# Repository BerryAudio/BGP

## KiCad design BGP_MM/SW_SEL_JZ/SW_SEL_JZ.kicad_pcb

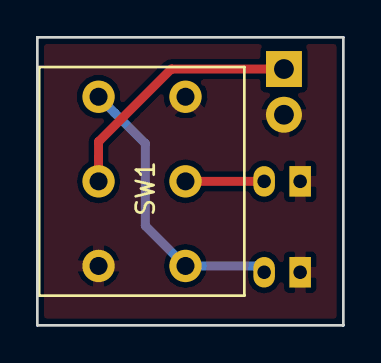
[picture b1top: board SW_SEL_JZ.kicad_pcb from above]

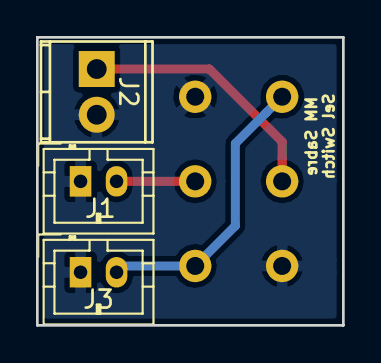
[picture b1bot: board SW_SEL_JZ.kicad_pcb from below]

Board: 2 copper layers, 17.0 x 16.0 mm, 4 parts (3 on the bottom side), 4 nets.

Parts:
J1, J3: Conn_01x02_Male; JST_PH_B2B-PH-K_02x2.00mm_Straight
J2: Screw_Terminal_01x02; TerminalBlock_Phoenix_MPT-2.54mm_2pol
SW1: Switch_SPDT_x2; NKK_DPDT

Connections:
/I_BR: J1.2, SW1.2
/I_NK: J2.1, SW1.5
/SIG_O: J3.2, SW1.3, SW1.4
Earth: J1.1, J2.2, J3.1, SW1.1, SW1.6

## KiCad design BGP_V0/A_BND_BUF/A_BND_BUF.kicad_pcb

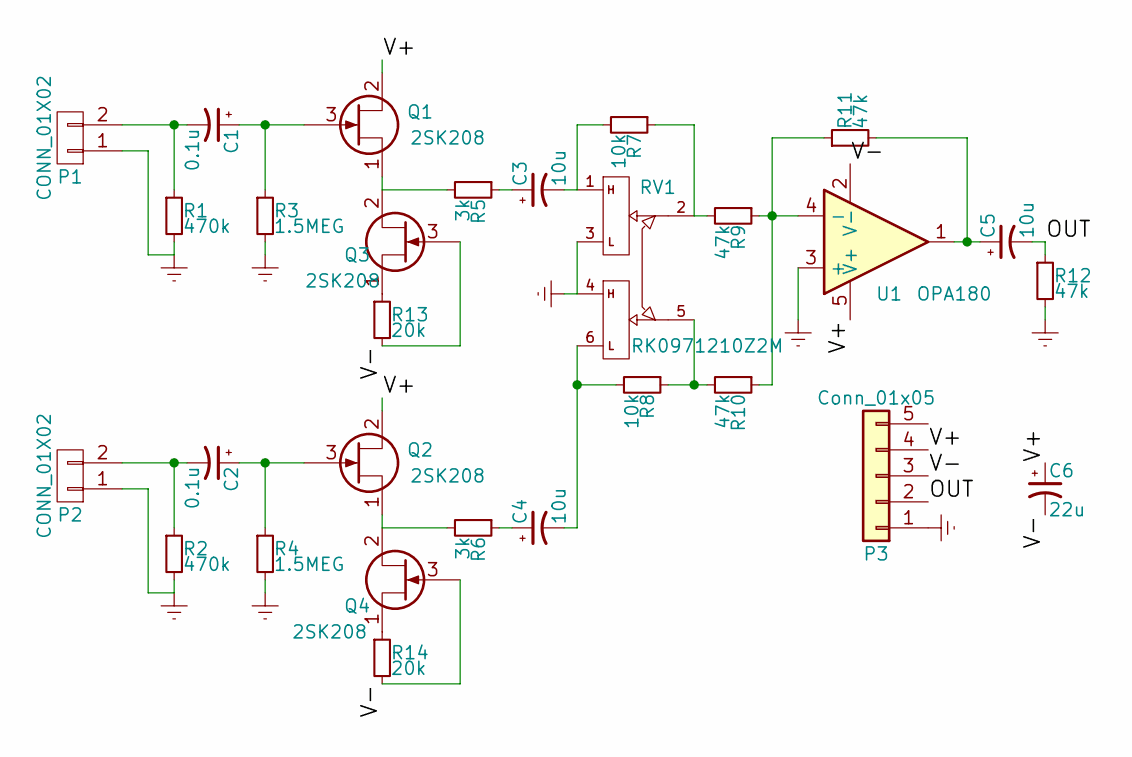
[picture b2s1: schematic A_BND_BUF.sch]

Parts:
C1, C2: 0.1u; TantalC_SizeR_EIA-2012
C3, C4, C5: 10u; TantalC_SizeS_EIA-3216
C6: 22u; C_0805_HandSoldering
P1, P2: CONN_01X02; TerminalBlock_Pheonix_MPT-2.54mm_2pol
P3: Conn_01x05; Molex_MicroLatch-53253-0570_05x2.00mm_Straight
Q1, Q2, Q3, Q4: 2SK208; SC-59_Handsoldering
R1, R2: 470k; R_0603_HandSoldering
R3, R4: 1.5MEG; R_0603_HandSoldering
R5, R6: 3k; R_0603_HandSoldering
R7, R8: 10k; R_0603_HandSoldering
R9, R10, R11, R12: 47k; R_0603_HandSoldering
R13, R14: 20k; R_0603_HandSoldering
RV1: RK0971210Z2M; Potentiometer_Alps_RK097_Double_Vertical
U1: OPA180; SOT-23-5_HandSoldering

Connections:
/OUT: C5.2, P3.2, R12.1
/V+: C6.1, P3.4, Q1.2 (D), Q2.2 (D), U1.5 (V+)
/V-: C6.2, P3.3, Q3.3 (G), Q4.3 (G), R13.2, R14.2, U1.2 (V-)
Earth: P1.1, P2.1, P3.1, R1.2, R2.2, R3.2, R4.2, R12.2, RV1.3, RV1.4, U1.3 (+)
unnamed: C1.1, Q1.3 (G), R3.1
unnamed: C1.2, P1.2, R1.1
unnamed: C2.1, Q2.3 (G), R4.1
unnamed: C2.2, P2.2, R2.1
unnamed: C3.1, R5.1
unnamed: C3.2, R7.2, RV1.1
unnamed: C4.1, R6.1
unnamed: C4.2, R8.2, RV1.6
unnamed: C5.1, R11.2, U1.1
unnamed: Q1.1 (S), Q3.2 (D), R5.2
unnamed: Q2.1 (S), Q4.2 (D), R6.2
unnamed: Q3.1 (S), R13.1
unnamed: Q4.1 (S), R14.1
unnamed: R7.1, R9.2, RV1.2
unnamed: R9.1, R10.1, R11.1, U1.4 (-)
unnamed: R8.1, R10.2, RV1.5

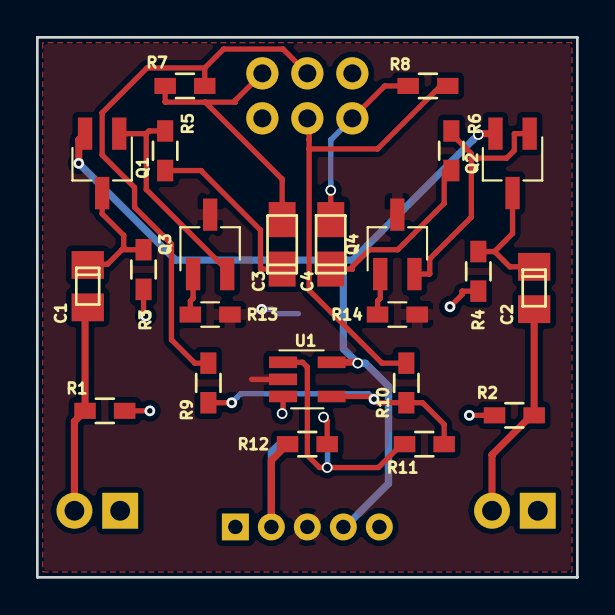
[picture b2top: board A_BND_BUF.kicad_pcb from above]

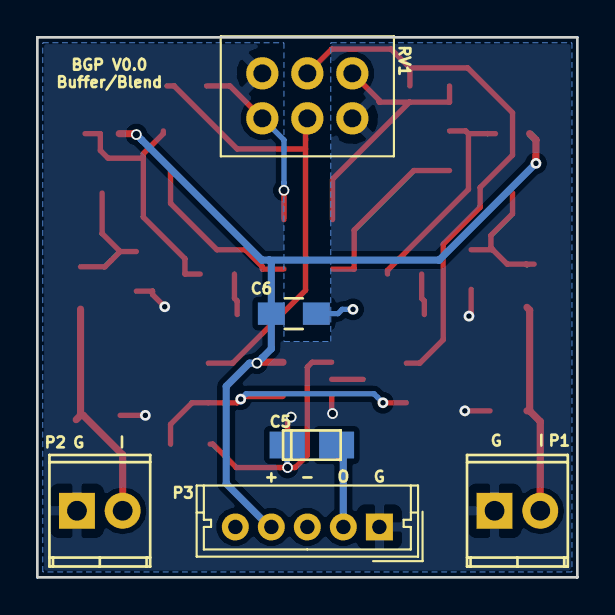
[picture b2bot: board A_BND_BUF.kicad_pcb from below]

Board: 2 copper layers, 30.0 x 30.0 mm, 29 parts (6 on the bottom side), 20 nets.

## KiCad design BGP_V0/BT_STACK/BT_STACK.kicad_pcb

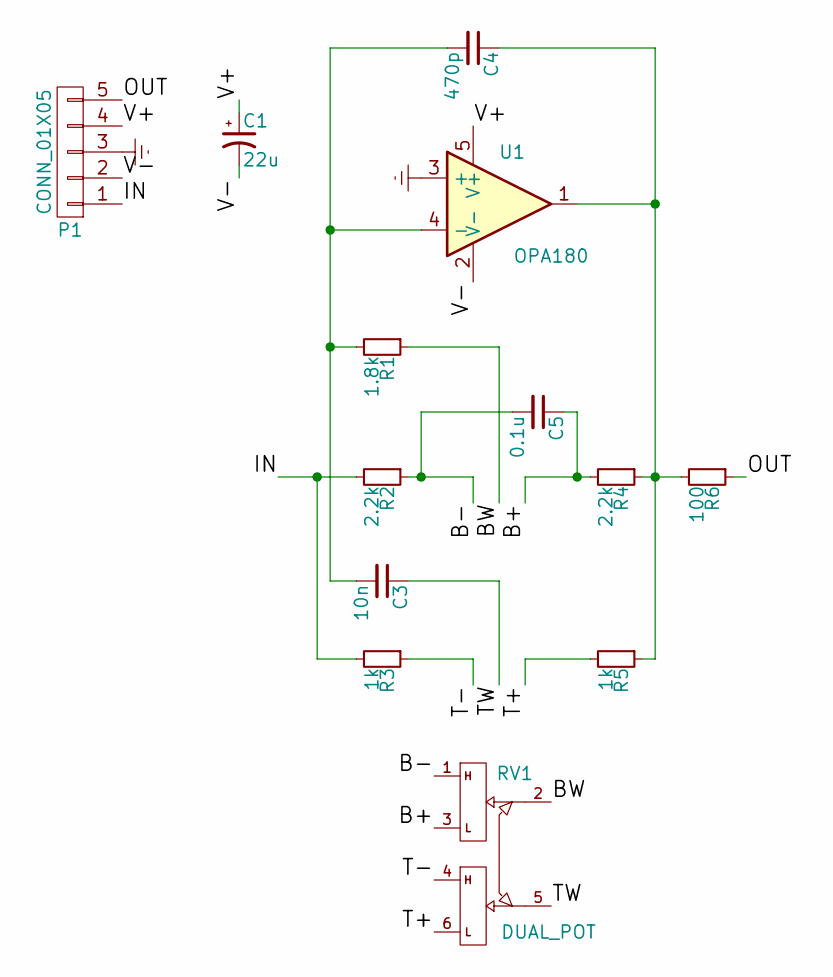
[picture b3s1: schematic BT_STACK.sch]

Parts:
C1: 22u; C_0805_HandSoldering
C3: 10n; C_0805_HandSoldering
C4: 470p; C_0805_HandSoldering
C5: 0.1u; C_0805_HandSoldering
P1: CONN_01X05; Molex_MicroLatch-53253-0570_05x2.00mm_Straight
R1: 1.8k; R_0603_HandSoldering
R2, R4: 2.2k; R_0603_HandSoldering
R3, R5: 1k; R_0603_HandSoldering
R6: 100; R_0603_HandSoldering
RV1: DUAL_POT; Potentiometer_Alps_RK097_Double_Vertical_Dual_Shaft
U1: OPA180; SOT-23-5_HandSoldering

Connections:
/B+: C5.1, R4.2, RV1.3
/B-: C5.2, R2.1, RV1.1
/BW: R1.1, RV1.2
/IN: P1.1, R2.2, R3.2
/OUT: P1.5, R6.1
/T+: R5.2, RV1.6
/T-: R3.1, RV1.4
/TW: C3.1, RV1.5
/V+: C1.1, P1.4, U1.5 (V+)
/V-: C1.2, P1.2, U1.2 (V-)
Earth: P1.3, U1.3 (+)
unnamed: C3.2, C4.2, R1.2, U1.4 (-)
unnamed: C4.1, R4.1, R5.1, R6.2, U1.1

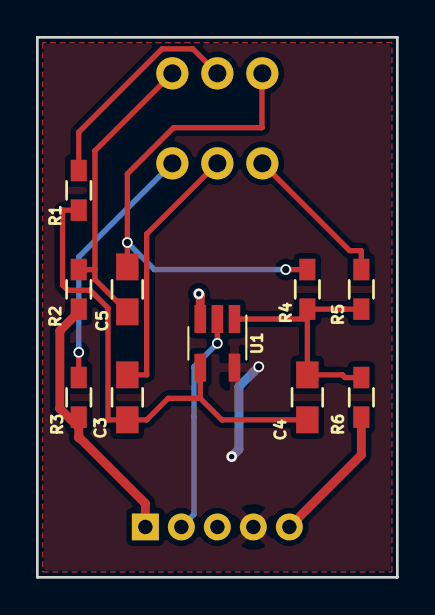
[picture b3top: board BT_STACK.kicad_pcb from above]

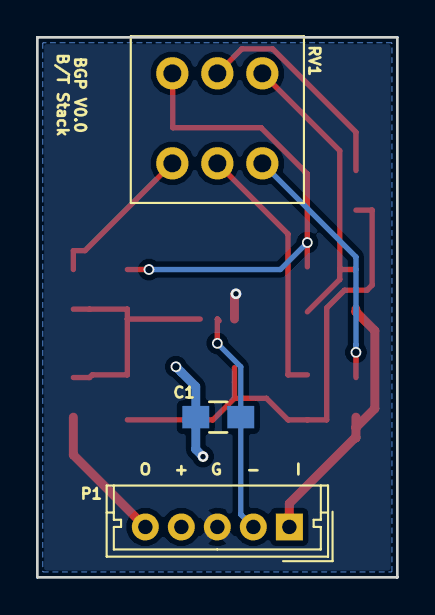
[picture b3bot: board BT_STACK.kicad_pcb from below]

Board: 2 copper layers, 20.0 x 30.0 mm, 13 parts (3 on the bottom side), 13 nets.

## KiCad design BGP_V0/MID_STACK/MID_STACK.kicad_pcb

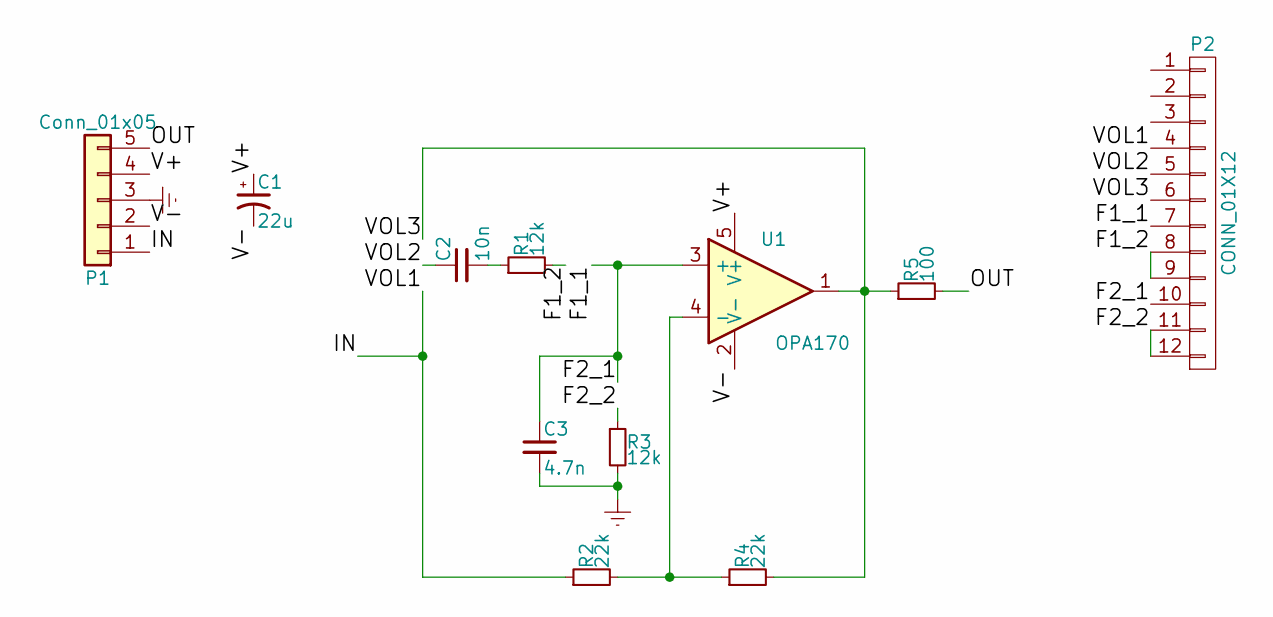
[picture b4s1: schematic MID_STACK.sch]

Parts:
C1: 22u; C_1206_HandSoldering
C2: 10n; C_0805_HandSoldering
C3: 4.7n; C_0805_HandSoldering
P1: Conn_01x05; Molex_MicroLatch-53253-0570_05x2.00mm_Straight
P2: CONN_01X12; Potentiometer_Alps_RK097_Quad_Vertical_Dual_Shaft
R1, R3: 12k; R_0603_HandSoldering
R2, R4: 22k; R_0603_HandSoldering
R5: 100; R_0603_HandSoldering
U1: OPA170; SOT-23-5_HandSoldering

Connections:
/F1_1: C3.1, P2.7, P2.10, U1.3 (+)
/F1_2: P2.8, P2.9, R1.2
/F2_2: P2.11, P2.12, R3.1
/IN: P1.1, P2.4, R2.1
/OUT: P1.5, R5.2
/V+: C1.1, P1.4, U1.5 (V+)
/V-: C1.2, P1.2, U1.2 (V-)
/VOL2: C2.1, P2.5
/VOL3: P2.6, R4.2, R5.1, U1.1
Earth: C3.2, P1.3, R3.2
unnamed: C2.2, R1.1
unnamed: R2.2, R4.1, U1.4 (-)

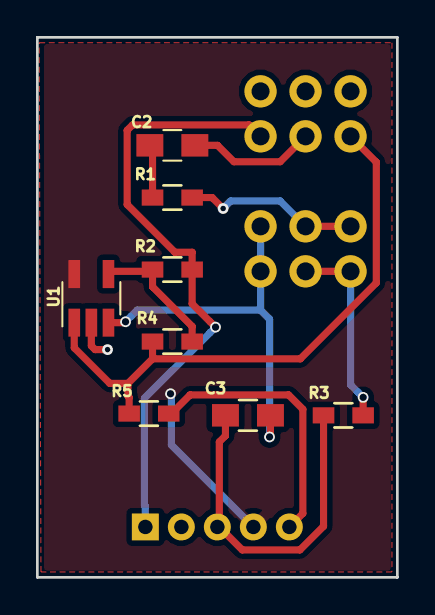
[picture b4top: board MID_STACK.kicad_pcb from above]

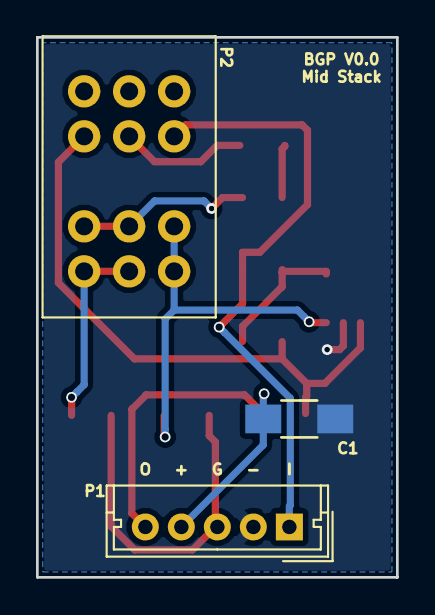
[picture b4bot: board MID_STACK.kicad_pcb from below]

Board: 2 copper layers, 20.0 x 30.0 mm, 11 parts (3 on the bottom side), 12 nets.

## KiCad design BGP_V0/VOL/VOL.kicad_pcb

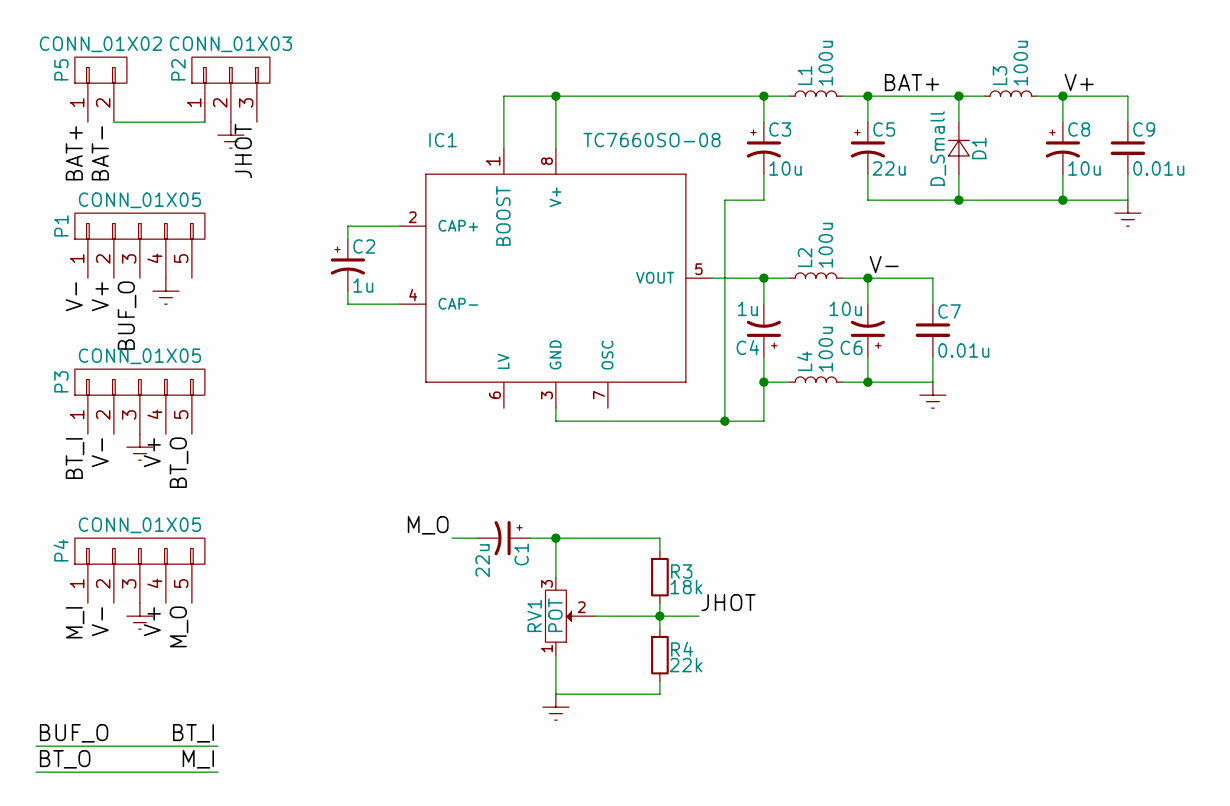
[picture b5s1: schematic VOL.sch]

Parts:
C1: 22u; TantalC_SizeR_EIA-2012
C2, C4: 1u; C_0805_HandSoldering
C3, C6, C8: 10u; C_0805_HandSoldering
C5: 22u; C_0805_HandSoldering
C7, C9: 0.01u; C_0603_HandSoldering
D1: D_Small; SOD-123
IC1: TC7660SO-08; SOIC-8_3.9x4.9mm_Pitch1.27mm
L1, L2, L3, L4: 100u; C_0805_HandSoldering
P1, P3, P4: CONN_01X05; Molex_MicroLatch-53253-0570_05x2.00mm_Straight
P2: CONN_01X03; TerminalBlock_Pheonix_MPT-2.54mm_3pol
P5: CONN_01X02; TerminalBlock_Pheonix_MPT-2.54mm_2pol
R3: 18k; R_0603_HandSoldering
R4: 22k; R_0603_HandSoldering
RV1: POT; Potentiometer_Alps_RK097_Single_Vertical

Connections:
/BAT+: C5.1, D1.1 (K), L1.2, L3.1, P5.1
/BAT-: P2.1, P5.2
/BT_I: P1.3, P3.1
/BT_O: P3.5, P4.1
/JHOT: P2.3, R3.2, R4.1, RV1.2
/M_O: C1.2, P4.5
/V+: C8.1, C9.1, L3.2, P1.2, P3.4, P4.4
/V-: C6.2, C7.1, L2.2, P1.1, P3.2, P4.2
Earth: C5.2, C6.1, C7.2, C8.2, C9.2, D1.2 (A), L4.2, P1.4, P2.2, P3.3, P4.3, R4.2, RV1.1
unnamed: C1.1, R3.1, RV1.3
unnamed: C2.1, IC1.2 (CAP+)
unnamed: C2.2, IC1.4 (CAP-)
unnamed: C3.1, IC1.1 (BOOST), IC1.8 (V+), L1.1
unnamed: C3.2, C4.1, IC1.3 (GND), L4.1
unnamed: C4.2, IC1.5 (VOUT), L2.1

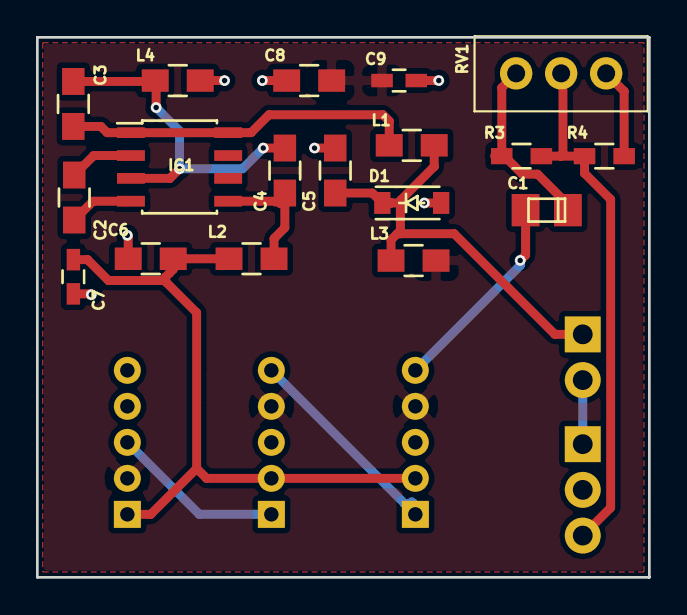
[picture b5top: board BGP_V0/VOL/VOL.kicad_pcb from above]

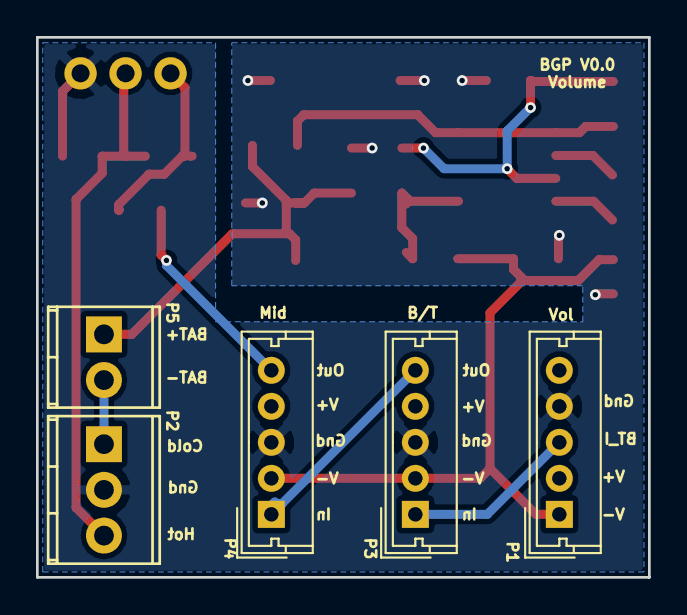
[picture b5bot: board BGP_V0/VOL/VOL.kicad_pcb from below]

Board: 2 copper layers, 34.0 x 30.0 mm, 23 parts (5 on the bottom side), 15 nets.

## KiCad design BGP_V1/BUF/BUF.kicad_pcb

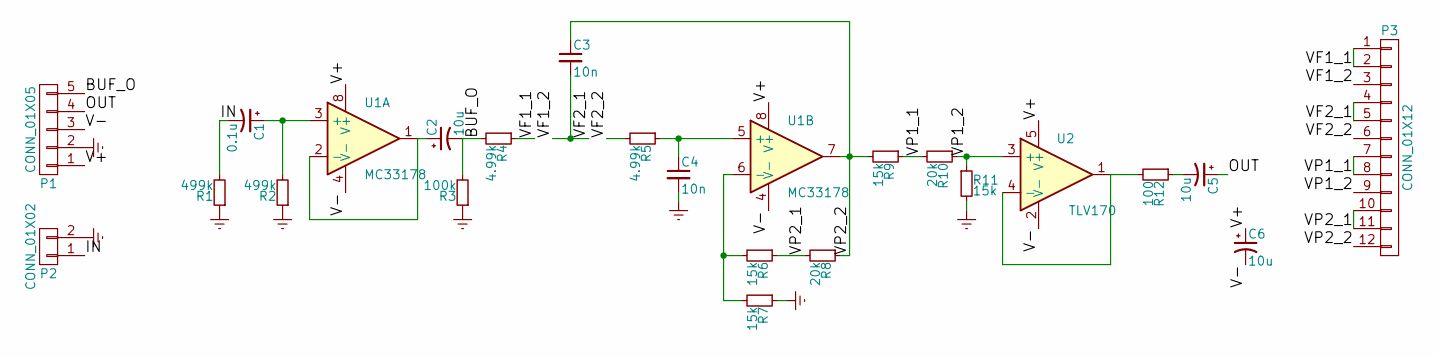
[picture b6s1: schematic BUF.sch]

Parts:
C1: 0.1u; C_0805_HandSoldering
C2, C5: 10u; TantalC_SizeS_EIA-3216
C3, C4: 10n; C_0805_HandSoldering
C6: 10u; C_0805_HandSoldering
P1: CONN_01X05; Molex_MicroLatch-53253-0570_05x2.00mm_Straight
P2: CONN_01X02; TerminalBlock_Pheonix_MPT-2.54mm_2pol
P3: CONN_01X12; Potentiometer_Alps_RK097_Quad_Vertical_Dual_Shaft
R1, R2: 499k; R_0603_HandSoldering
R3: 100k; R_0603_HandSoldering
R4, R5: 4.99k; R_0603_HandSoldering
R6, R7, R9, R11: 15k; R_0603_HandSoldering
R8, R10: 20k; R_0603_HandSoldering
R12: 100; R_0603_HandSoldering
U1: MC33178; SOIC-8_3.9x4.9mm_Pitch1.27mm
U2: TLV170; SOT-23-5_HandSoldering

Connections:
/BUF_O: C2.2, P1.5, R3.2, R4.2
/IN: C1.2, P2.1, R1.2
/OUT: C5.1, P1.4
/V+: C6.1, P1.1, U1.8 (V+), U2.5 (V+)
/V-: C6.2, P1.3, U1.4 (V-), U2.2 (V-)
/VF1_1: P3.1, P3.2, R4.1
/VF1_2: C3.2, P3.3, P3.4, P3.5
/VF2_2: P3.6, R5.2
/VP1_1: P3.7, P3.8, R9.1, R10.2
/VP1_2: P3.9, R10.1, R11.1, U2.3 (+)
/VP2_1: P3.10, P3.11, R6.1, R8.2
/VP2_2: C3.1, P3.12, R8.1, R9.2, U1.7
Earth: C4.2, P1.2, P2.2, R1.1, R2.1, R3.1, R7.1, R11.2
unnamed: C1.1, R2.2, U1.3 (+)
unnamed: C2.1, U1.1, U1.2 (-)
unnamed: C4.1, R5.1, U1.5 (+)
unnamed: C5.2, R12.1
unnamed: R6.2, R7.2, U1.6 (-)
unnamed: R12.2, U2.1, U2.4 (-)

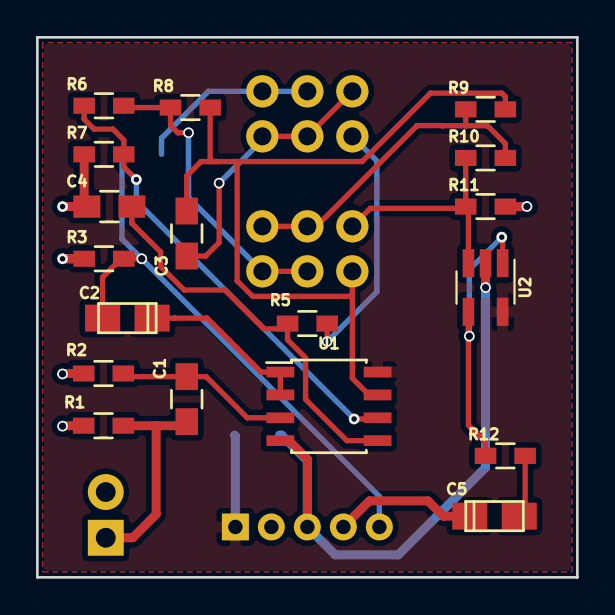
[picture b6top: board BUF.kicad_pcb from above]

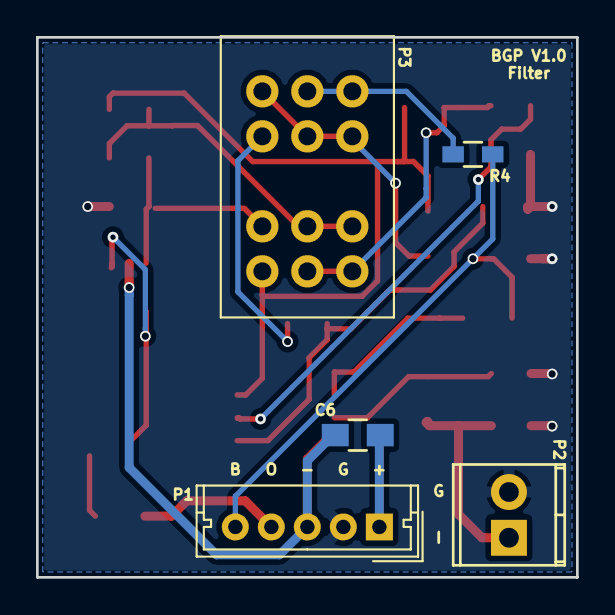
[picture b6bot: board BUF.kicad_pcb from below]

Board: 2 copper layers, 30.0 x 30.0 mm, 23 parts (5 on the bottom side), 19 nets.

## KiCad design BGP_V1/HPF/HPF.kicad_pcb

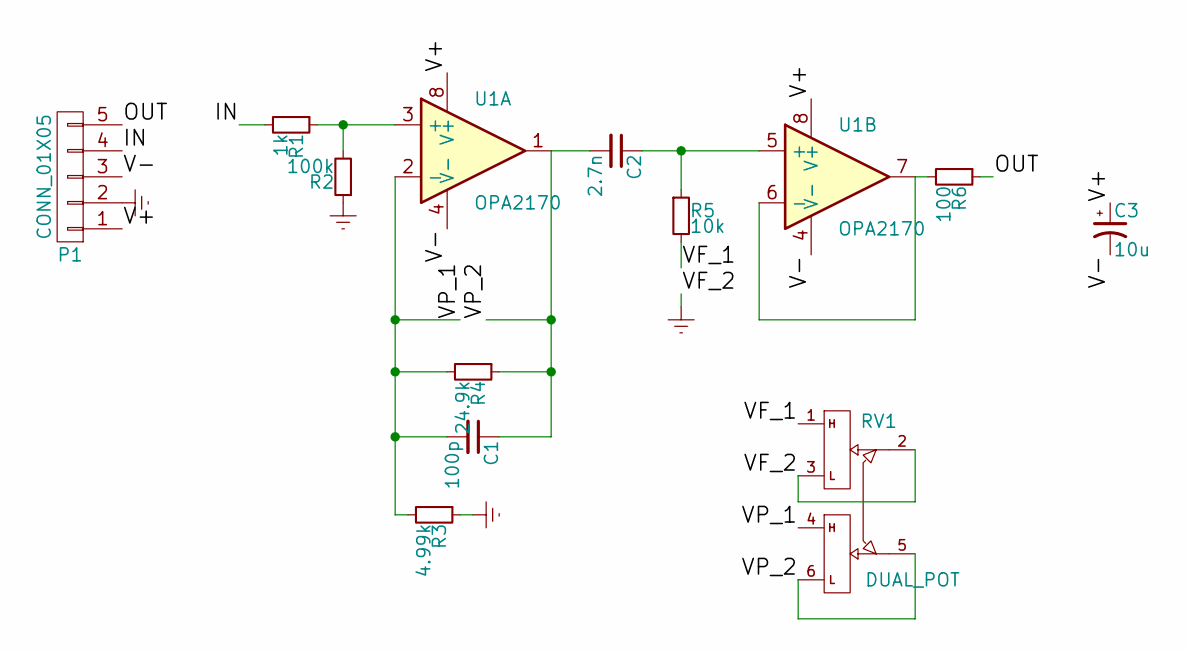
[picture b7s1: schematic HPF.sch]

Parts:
C1: 100p; C_0805_HandSoldering
C2: 2.7n; C_0805_HandSoldering
C3: 10u; C_0805_HandSoldering
P1: CONN_01X05; Molex_MicroLatch-53253-0570_05x2.00mm_Straight
R1: 1k; R_0603_HandSoldering
R2: 100k; R_0603_HandSoldering
R3: 4.99k; R_0603_HandSoldering
R4: 24.9k; R_0603_HandSoldering
R5: 10k; R_0603_HandSoldering
R6: 100; R_0603_HandSoldering
RV1: DUAL_POT; Potentiometer_Alpha_Double_Vertical_Dual_Shaft
U1: OPA2170; SOIC-8_3.9x4.9mm_Pitch1.27mm

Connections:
/IN: P1.4, R1.2
/OUT: P1.5, R6.1
/V+: C3.1, P1.1, U1.8 (V+)
/V-: C3.2, P1.3, U1.4 (V-)
/VF_1: R5.2, RV1.1
/VP_1: C1.2, R3.2, R4.2, RV1.4, U1.2 (-)
/VP_2: C1.1, C2.2, R4.1, RV1.5, RV1.6, U1.1
Earth: P1.2, R2.1, R3.1, RV1.2, RV1.3
unnamed: C2.1, R5.1, U1.5 (+)
unnamed: R1.1, R2.2, U1.3 (+)
unnamed: R6.2, U1.6 (-), U1.7

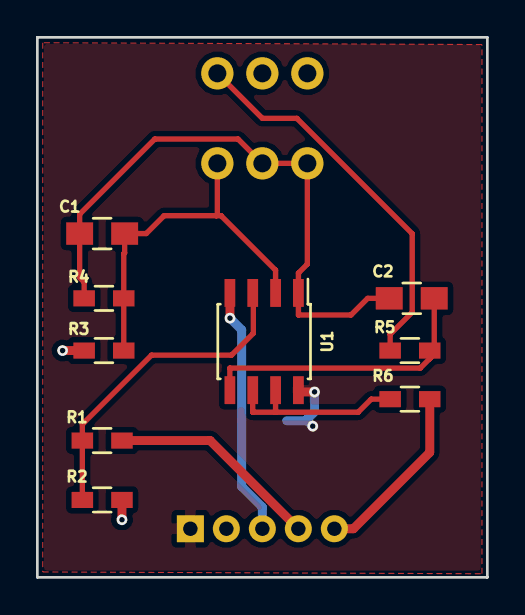
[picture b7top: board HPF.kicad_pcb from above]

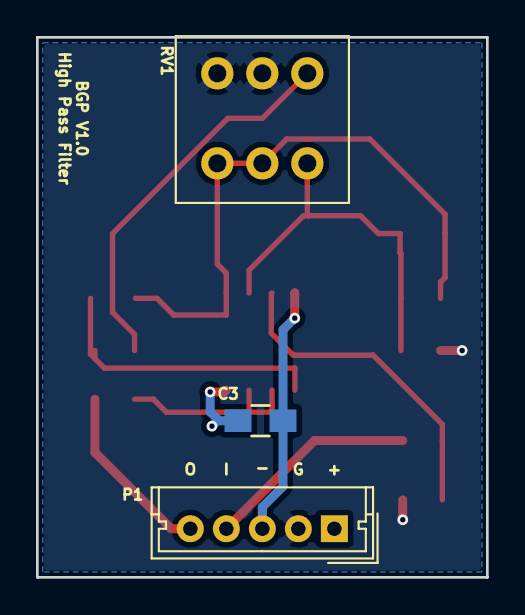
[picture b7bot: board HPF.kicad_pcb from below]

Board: 2 copper layers, 25.0 x 30.0 mm, 12 parts (3 on the bottom side), 11 nets.
